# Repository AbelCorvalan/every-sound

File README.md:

# EverySound

## Videitos 🎸:
* https://www.youtube.com/@arito
* https://www.youtube.com/@Lantertronics 
* https://www.youtube.com/@DiyguitarpedalsAu (usa LTspice)

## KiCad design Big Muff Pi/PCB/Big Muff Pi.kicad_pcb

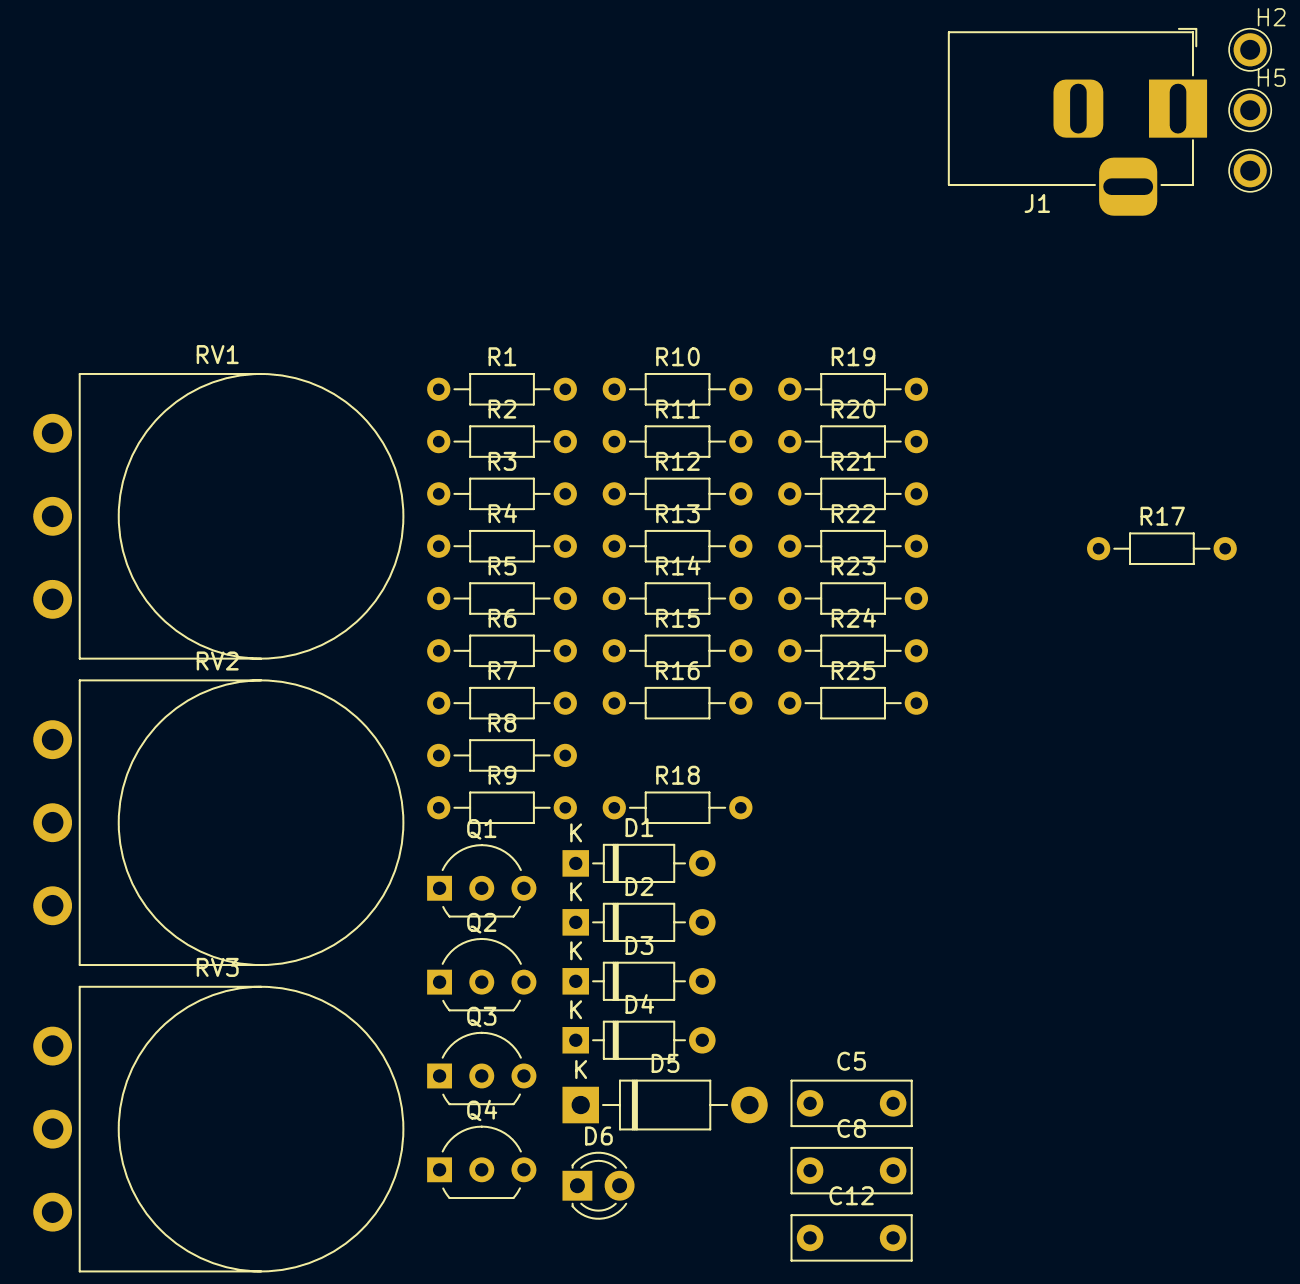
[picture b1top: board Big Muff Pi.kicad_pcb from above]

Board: 2 copper layers, 45 parts (0 on the bottom side), 24 nets, no tracks yet.

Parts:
C5, C8, C12: 0.1u; C_Rect_L7.0mm_W2.5mm_P5.00mm
D1, D2, D3, D4: 1N914; D_DO-35_SOD27_P7.62mm_Horizontal
D5: 1N4001; D_DO-41_SOD81_P10.16mm_Horizontal
D6: LED; LED_D3.0mm_Clear
H1: IN; MountingHole-1.2mm
H2: OUT; MountingHole-1.2mm
H5: SW; MountingHole-1.2mm
J1: Barrel_Jack_MountingPin; BarrelJack_Horizontal
Q1, Q2, Q3, Q4: NPN; TO-92L_Inline_Wide
R1, R17: 39k; R_Axial_DIN0204_L3.6mm_D1.6mm_P7.62mm_Horizontal
R2, R8, R13, R18, R19: 100k; R_Axial_DIN0204_L3.6mm_D1.6mm_P7.62mm_Horizontal
R3, R9, R14: 470k; R_Axial_DIN0204_L3.6mm_D1.6mm_P7.62mm_Horizontal
R4, R10, R15: 15k; R_Axial_DIN0204_L3.6mm_D1.6mm_P7.62mm_Horizontal
R5, R11, R16: 100; R_Axial_DIN0204_L3.6mm_D1.6mm_P7.62mm_Horizontal
R6: 1k; R_Axial_DIN0204_L3.6mm_D1.6mm_P7.62mm_Horizontal
R7, R12: 8.2k; R_Axial_DIN0204_L3.6mm_D1.6mm_P7.62mm_Horizontal
R20: 390k; R_Axial_DIN0204_L3.6mm_D1.6mm_P7.62mm_Horizontal
R21: 10k; R_Axial_DIN0204_L3.6mm_D1.6mm_P7.62mm_Horizontal
R22: 2.2k; R_Axial_DIN0204_L3.6mm_D1.6mm_P7.62mm_Horizontal
R23: 1Mega; R_Axial_DIN0204_L3.6mm_D1.6mm_P7.62mm_Horizontal
R24: 100K; R_Axial_DIN0204_L3.6mm_D1.6mm_P7.62mm_Horizontal
R25: 4.7K; R_Axial_DIN0204_L3.6mm_D1.6mm_P7.62mm_Horizontal
RV1, RV2, RV3: 100k; Potentiometer_Omeg_PC16BU_Vertical_Edit

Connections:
+9v: D5.1 (K), J1.1, R4.2, R10.1, R15.1, R20.2, R21.2, R24.2, R25.2
A: C8.2, Q3.1 (C), R14.1, R15.2, R17.1
GND: D5.2 (A), J1.2, R2.2, R5.1, R6.1, R8.1, R11.2, R13.1, R16.2, R18.1, R19.1, R22.1, R23.1, RV3.3
unnamed: R18.2, RV2.1
unnamed: R17.2, RV2.3
unnamed: C12.1, RV2.2
unnamed: D1.2 (A), D2.1 (K), Q2.2 (B), R7.2, R8.2, R9.2
unnamed: C5.1, D1.1 (K), D2.2 (A)
unnamed: D3.2 (A), D4.1 (K), Q3.2 (B), R12.2, R13.2, R14.2
unnamed: C8.1, D3.1 (K), D4.2 (A)
unnamed: D6.2 (A), R25.1
unnamed: D6.1 (K), H5.1
unnamed: H1.1, R1.1, R23.2
unnamed: H2.1, RV3.2
unnamed: Q1.2 (B), R2.1, R3.1
unnamed: Q1.1 (C), R3.2, R4.1
unnamed: Q1.3 (E), R5.2
unnamed: C5.2, Q2.1 (C), R9.1, R10.2
unnamed: Q2.3 (E), R11.1
unnamed: Q3.3 (E), R16.1
unnamed: C12.2, Q4.2 (B), R19.2, R20.1
unnamed: Q4.1 (C), R21.1
unnamed: Q4.3 (E), R22.2
unnamed: R6.2, RV1.3

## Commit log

2025-02-19 Initialize repository
2025-02-19 Get components script added
2025-02-19 Kicad values loader in process (read principal columns)
2025-03-08 Add info, 3D Model Enclousure, Filter Simulation
2025-03-10 Modify CADs. Add draws
